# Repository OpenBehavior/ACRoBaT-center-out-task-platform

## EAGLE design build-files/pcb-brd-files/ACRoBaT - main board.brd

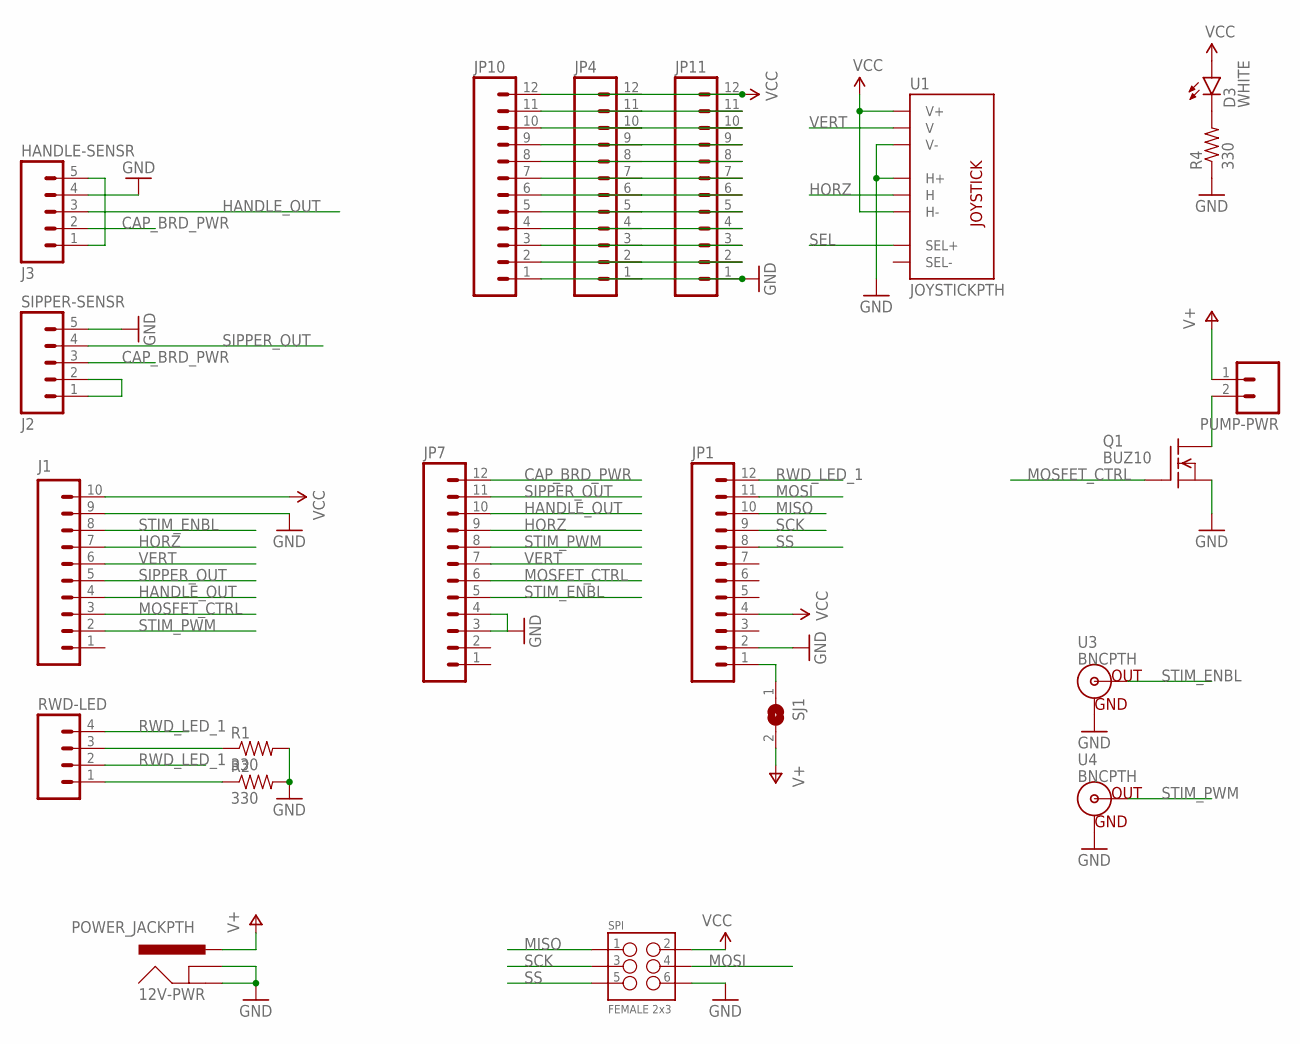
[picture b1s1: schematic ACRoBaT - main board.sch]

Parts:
12V-PWR: POWER_JACKPTH; POWER_JACK_PTH
D3: WHITE; LED-1206
HANDLE-SENSR: J3; 1X05
J1: M10SILK_FEMALE_PTH; 1X10
JP1, JP4, JP7, JP10, JP11: M12PTH; 1X12
PUMP-PWR: M02PTH; 1X02
Q1: BUZ10; TO220
R1, R2, R4: 330; AXIAL-0.3
RWD-LED: M04PTH; 1X04
SIPPER-SENSR: J2; 1X05
SJ1: SJ
SPI: FEMALE 2x3; 2X3
U1: JOYSTICKPTH; JOYSTICK
U3, U4: BNCPTH; BNC

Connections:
CAP_BRD_PWR: HANDLE-SENSR.2, JP7.12, SIPPER-SENSR.3
GND: 12V-PWR.GND, 12V-PWR.GNDBREAK, HANDLE-SENSR.4, J1.9, JP1.2, JP4.1, JP7.3, JP7.4, JP10.1, JP11.1, Q1.3 (S), R1.P$2 (2), R2.P$2 (2), R4.P$1 (1), SIPPER-SENSR.5, SPI.6, U1.H1 (H+), U1.V3 (V-), U3.GND, U4.GND
HANDLE_OUT: HANDLE-SENSR.3, J1.4, JP7.10
HORZ: J1.7, JP7.9, U1.H2 (H)
MISO: JP1.10, SPI.1
MOSFET_CTRL: J1.3, JP7.6, Q1.1 (G)
MOSI: JP1.11, SPI.4
unnamed: HANDLE-SENSR.1, HANDLE-SENSR.5
unnamed: SIPPER-SENSR.1, SIPPER-SENSR.2
unnamed: D3.C, R4.P$2 (2)
unnamed: JP4.11, JP10.11, JP11.11
unnamed: R1.P$1 (1), RWD-LED.3
unnamed: R2.P$1 (1), RWD-LED.1
unnamed: JP4.10, JP10.10, JP11.10
unnamed: JP4.9, JP10.9, JP11.9
unnamed: JP4.8, JP10.8, JP11.8
unnamed: JP4.7, JP10.7, JP11.7
unnamed: JP4.6, JP10.6, JP11.6
unnamed: JP4.5, JP10.5, JP11.5
unnamed: JP4.4, JP10.4, JP11.4
unnamed: JP4.3, JP10.3, JP11.3
unnamed: JP4.2, JP10.2, JP11.2
unnamed: PUMP-PWR.2, Q1.2 (D)
unnamed: JP1.1, SJ1.1
RWD_LED_1: JP1.12, RWD-LED.2, RWD-LED.4
SCK: JP1.9, SPI.3
SEL: U1.B1A (SEL+)
SIPPER_OUT: J1.5, JP7.11, SIPPER-SENSR.4
SS: JP1.8, SPI.5
STIM_ENBL: J1.8, JP7.5, U3.S (OUT)
STIM_PWM: J1.2, JP7.8, U4.S (OUT)
V+: 12V-PWR.PWR, PUMP-PWR.1, SJ1.2
VCC: D3.A, J1.10, JP1.4, JP4.12, JP10.12, JP11.12, SPI.2, U1.H3 (H-), U1.V1 (V+)
VERT: J1.6, JP7.7, U1.V2 (V)

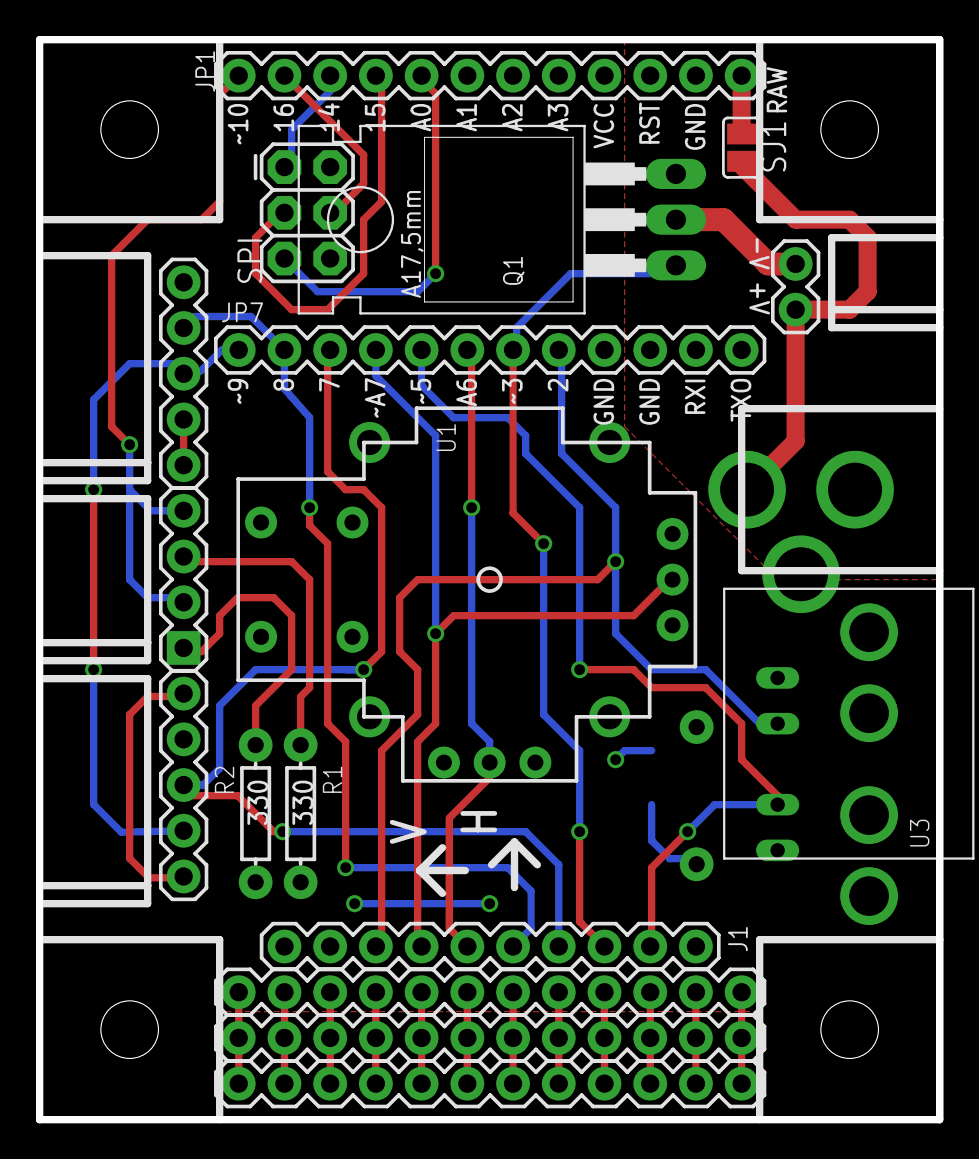
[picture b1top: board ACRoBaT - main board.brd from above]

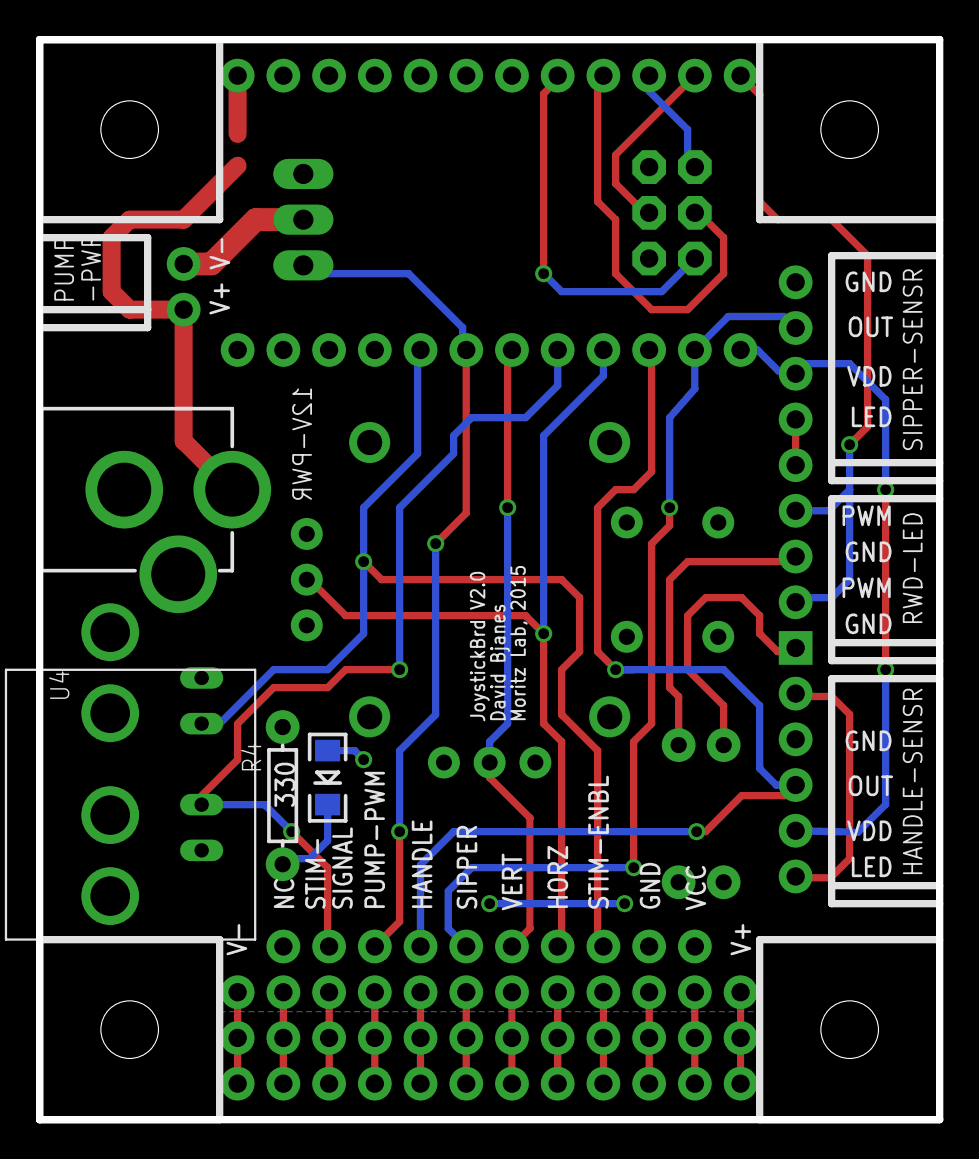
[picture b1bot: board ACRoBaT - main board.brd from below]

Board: 2 copper layers, 50.0 x 60.0 mm, 21 parts (4 on the bottom side), 33 nets.

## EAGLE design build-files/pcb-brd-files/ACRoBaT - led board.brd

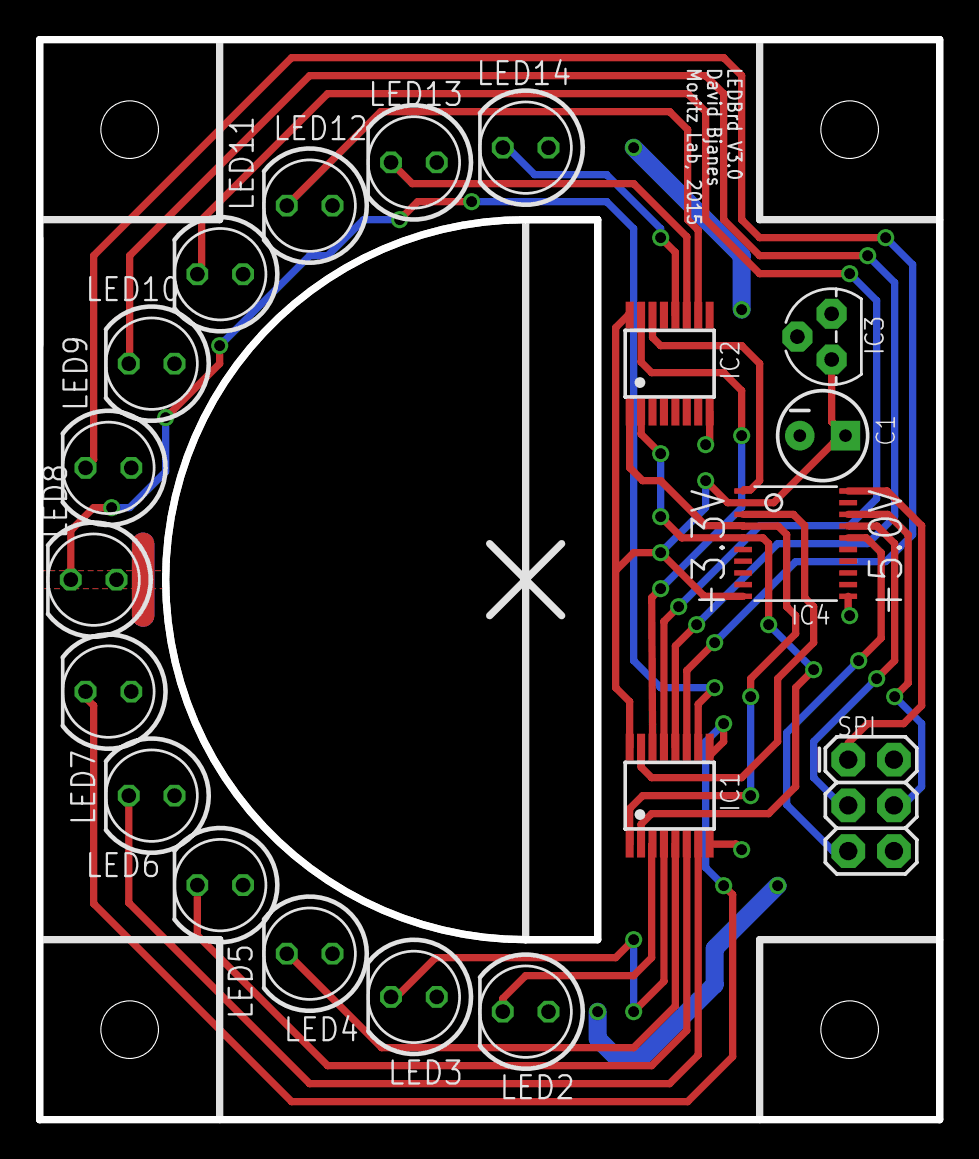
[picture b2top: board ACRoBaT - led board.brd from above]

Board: 2 copper layers, 50.0 x 60.0 mm, 19 parts (0 on the bottom side), 25 nets.

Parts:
C1: 10uF; CPOL-RADIAL-10UF-25V
IC1, IC2: QSOP16
IC3: L4931-3.3; TO92
IC4: TSSOP20
LED2, LED3, LED4, LED5, LED6, LED7, LED8, LED9, LED10, LED11, LED12, LED13, LED14: LED5MM
SPI: FEMALE 2x3; 2X3

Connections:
3.3V: C1.1, IC1.16, IC2.16, IC3.1, IC4.2, IC4.10
DOUT_3.3V: IC1.14, IC2.15
GND: C1.2, IC1.8, IC2.8, IC3.2, IC4.11, SPI.6
MISO_3.3V: IC2.14, IC4.1
MISO_5V: IC4.20, SPI.1
MOSI_3.3V: IC1.15, IC4.3
MOSI_5V: IC4.18, SPI.4
unnamed: IC1.3, LED2.K
unnamed: IC1.4, LED3.K
unnamed: IC1.5, LED4.K
unnamed: IC1.6, LED5.K
unnamed: IC1.7, LED6.K
unnamed: IC1.9, LED7.K
unnamed: IC1.10, LED8.K
unnamed: IC1.11, LED9.K
unnamed: IC1.12, LED10.K
unnamed: IC1.13, LED11.K
unnamed: IC2.10, LED12.K
unnamed: IC2.11, LED13.K
unnamed: IC2.12, LED14.K
SCK_3.3V: IC1.1, IC2.1, IC4.4
SCK_5V: IC4.17, SPI.3
SS_3.3V: IC1.2, IC2.2, IC4.5
SS_5V: IC4.16, SPI.5
VCC: IC3.3, IC4.19, LED2.A, LED3.A, LED4.A, LED5.A, LED6.A, LED7.A, LED8.A, LED9.A, LED10.A, LED11.A, LED12.A, LED13.A, LED14.A, SPI.2

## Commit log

2017-10-11 updated folder structure
2017-10-12 updated videos
2017-10-26 Updated files

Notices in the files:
parts and their libraries:
SparkFun-Connectors: Licensing: Creative Commons ShareAlike 4.0 International - https://creativecommons.org/licenses/by-sa/4.0
